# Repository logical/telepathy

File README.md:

THIS PROJECT IS DISCONTINUED FOR NOW.

The research is proving more difficult than I have hoped and there are alternatives available.

This is telepathy the mostly HARDWARE project not telepathy the software project
Sorry for my lack of creativity in choosing a name.

This poject contains an EXPERIMENTAL wireless eeg circuit.

GOAL
------
This project is under development so it is not working. I welcome suggestions.

The goal is to do brain computer interface experments.I want to make a wireless headband that runs
on a battery. 

It contains.

STATUS
------
I made one pcb but it didn't work. I'm still interested in the project so I am currently doing 
a complete redesign of the hardware. I will be etching the boards myself they will be single sided SMT 
and divided in sections.Here are some of the changes I'm planning. 

1. Split the device into sections for power, amplifier and input/output.
2. Replace the wireless module and pic with a wireless capable microcontroller. (telepathy with esp8266?)
3. The whole design will be based on active electrodes.

ELECTRODES: 

I have 2 designs for active electrodes. Active dry electrodes and active noncontact electrodes.
The dry electrodes are based on the openeeg design. The noncontact electrodes are based on a design I found here:

http://www.isn.ucsd.edu/pubs/bsn10.pdf

I'm assuming it is creative commons.

AMPLIFIER BOARD:

The amplifier board is under testing I plan to use one filter for aliasing and filter the rest in software. None
 of the resistor and capacitor values are decided yet.  
I have the source voltage at 3.3v from a cell phone battery. So far I can pick up a heartbeat .

EEGDATA:

A GUI software program for linux that retreives the data from the /dev/rfcomm0 bluetooth serial terminal
and analyzes and displays the data. I started the project in C but it was more convenient to write the data analysis portion in C++. 

On my system I use these commands to setup the bluetooth serial port.

 	#find the address
 	$hcitool scan
	#bind the address
	$sudo rfcomm bind rfcomm0 device_address
	
For BLE

	#find the adapter address
	$hcitool dev
	#find the device address
	$sudo hcitool -i hci0 lescan

Then you need to run any programs that access serial terminal as root unless you have sufficient permission.

FIRMWARE:

The firmware is for a PIC microcontroller 16f1788 and a bluetooth serial module hc-05.

I have wrote a bootloader so I can more easily install firmware.The bootloader sets the hc-05 up at 38400 and waits for a program.
When the program successfully loads it sets a byte in ee memory.when the FLASH command is sent to the program it erases the byte
so the bootloader will again wait for a progam. You can use a standard serial terminal to send the program but you have to set a long delay (~30ms) between characters so the program has time to write. Custom coding the serial interface for the bootloader would be faster but this works for now.

Hopefully I have no glitches in the bootloader or a firmware update could brick the device! 
If so the glitch would have to be fixed and the bootloader reprogrammed.

The microcontroller first sets up the hc-05 at 230400, then wait for a request.When it receives  a request it begins sampling the analog to digital converter and sending the samples to the hc-05.

I have included the makefiles so they should build with the make command but they may require modification . MPLABX should be able to load them as a makefile project but I have not tried.

SCHEMATIC:

I'm developing the amplifier board first. amplifier-board.png is the current design.

DISCLAIMER:

This project is an EXPERIMENT. I make no claims that it actually does anything.It may be harmful to 
individuals or property.
THIS DEVICE AND SOFTWARE MAY BE DANGEROUS. DO NOT BUILD IT.

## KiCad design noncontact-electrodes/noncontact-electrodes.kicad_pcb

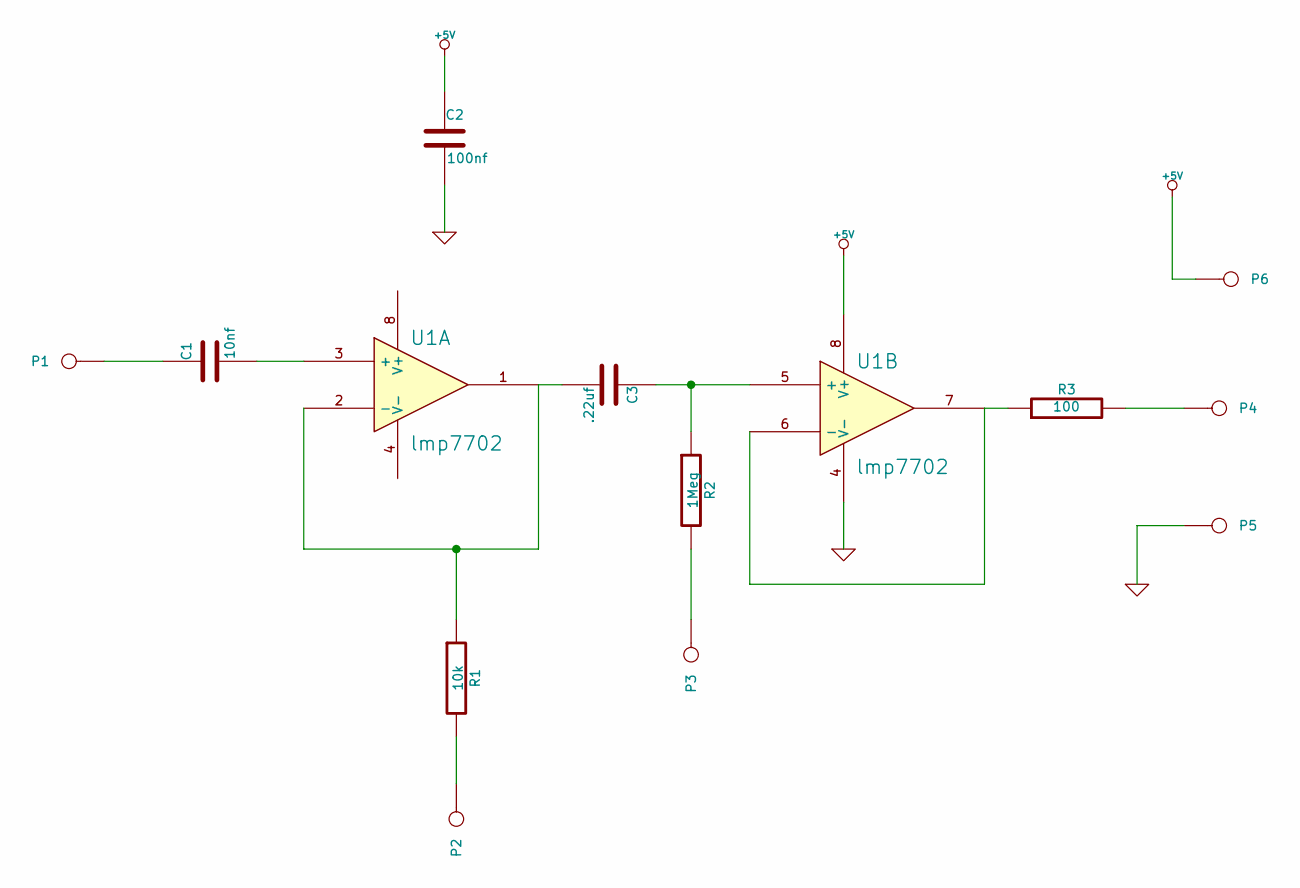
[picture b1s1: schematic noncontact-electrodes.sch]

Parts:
C1: 10nf
C2: 100nf
C3: .22uf
P1, P2, P3, P4, P5, P6: CONN_1
R1: 10k
R2: 1Meg
R3: 100
U1: lmp7702

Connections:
+5V: C2.1, P6.1, U1.8 (V+)
GND: C2.2, P5.1, U1.4 (V-)
unnamed: P2.1, R1.2
unnamed: C1.1, P1.1
unnamed: P4.1, R3.2
unnamed: P3.1, R2.2
unnamed: C1.2, U1.3 (+)
unnamed: C3.2, R1.1, U1.1, U1.2 (-)
unnamed: R3.1, U1.6 (-), U1.7
unnamed: C3.1, R2.1, U1.5 (+)

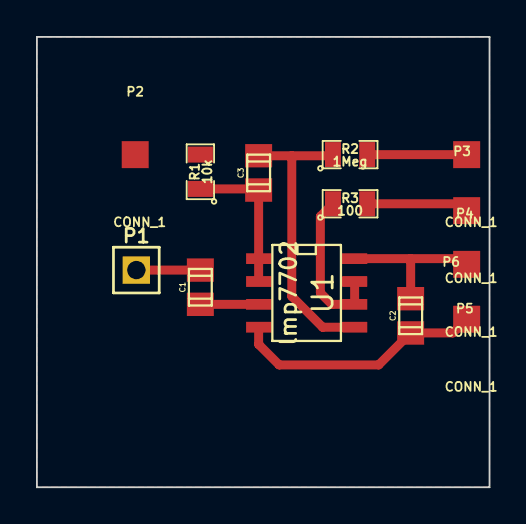
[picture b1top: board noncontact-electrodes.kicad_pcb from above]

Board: 2 copper layers, 25.1 x 25.0 mm, 13 parts (0 on the bottom side), 10 nets.

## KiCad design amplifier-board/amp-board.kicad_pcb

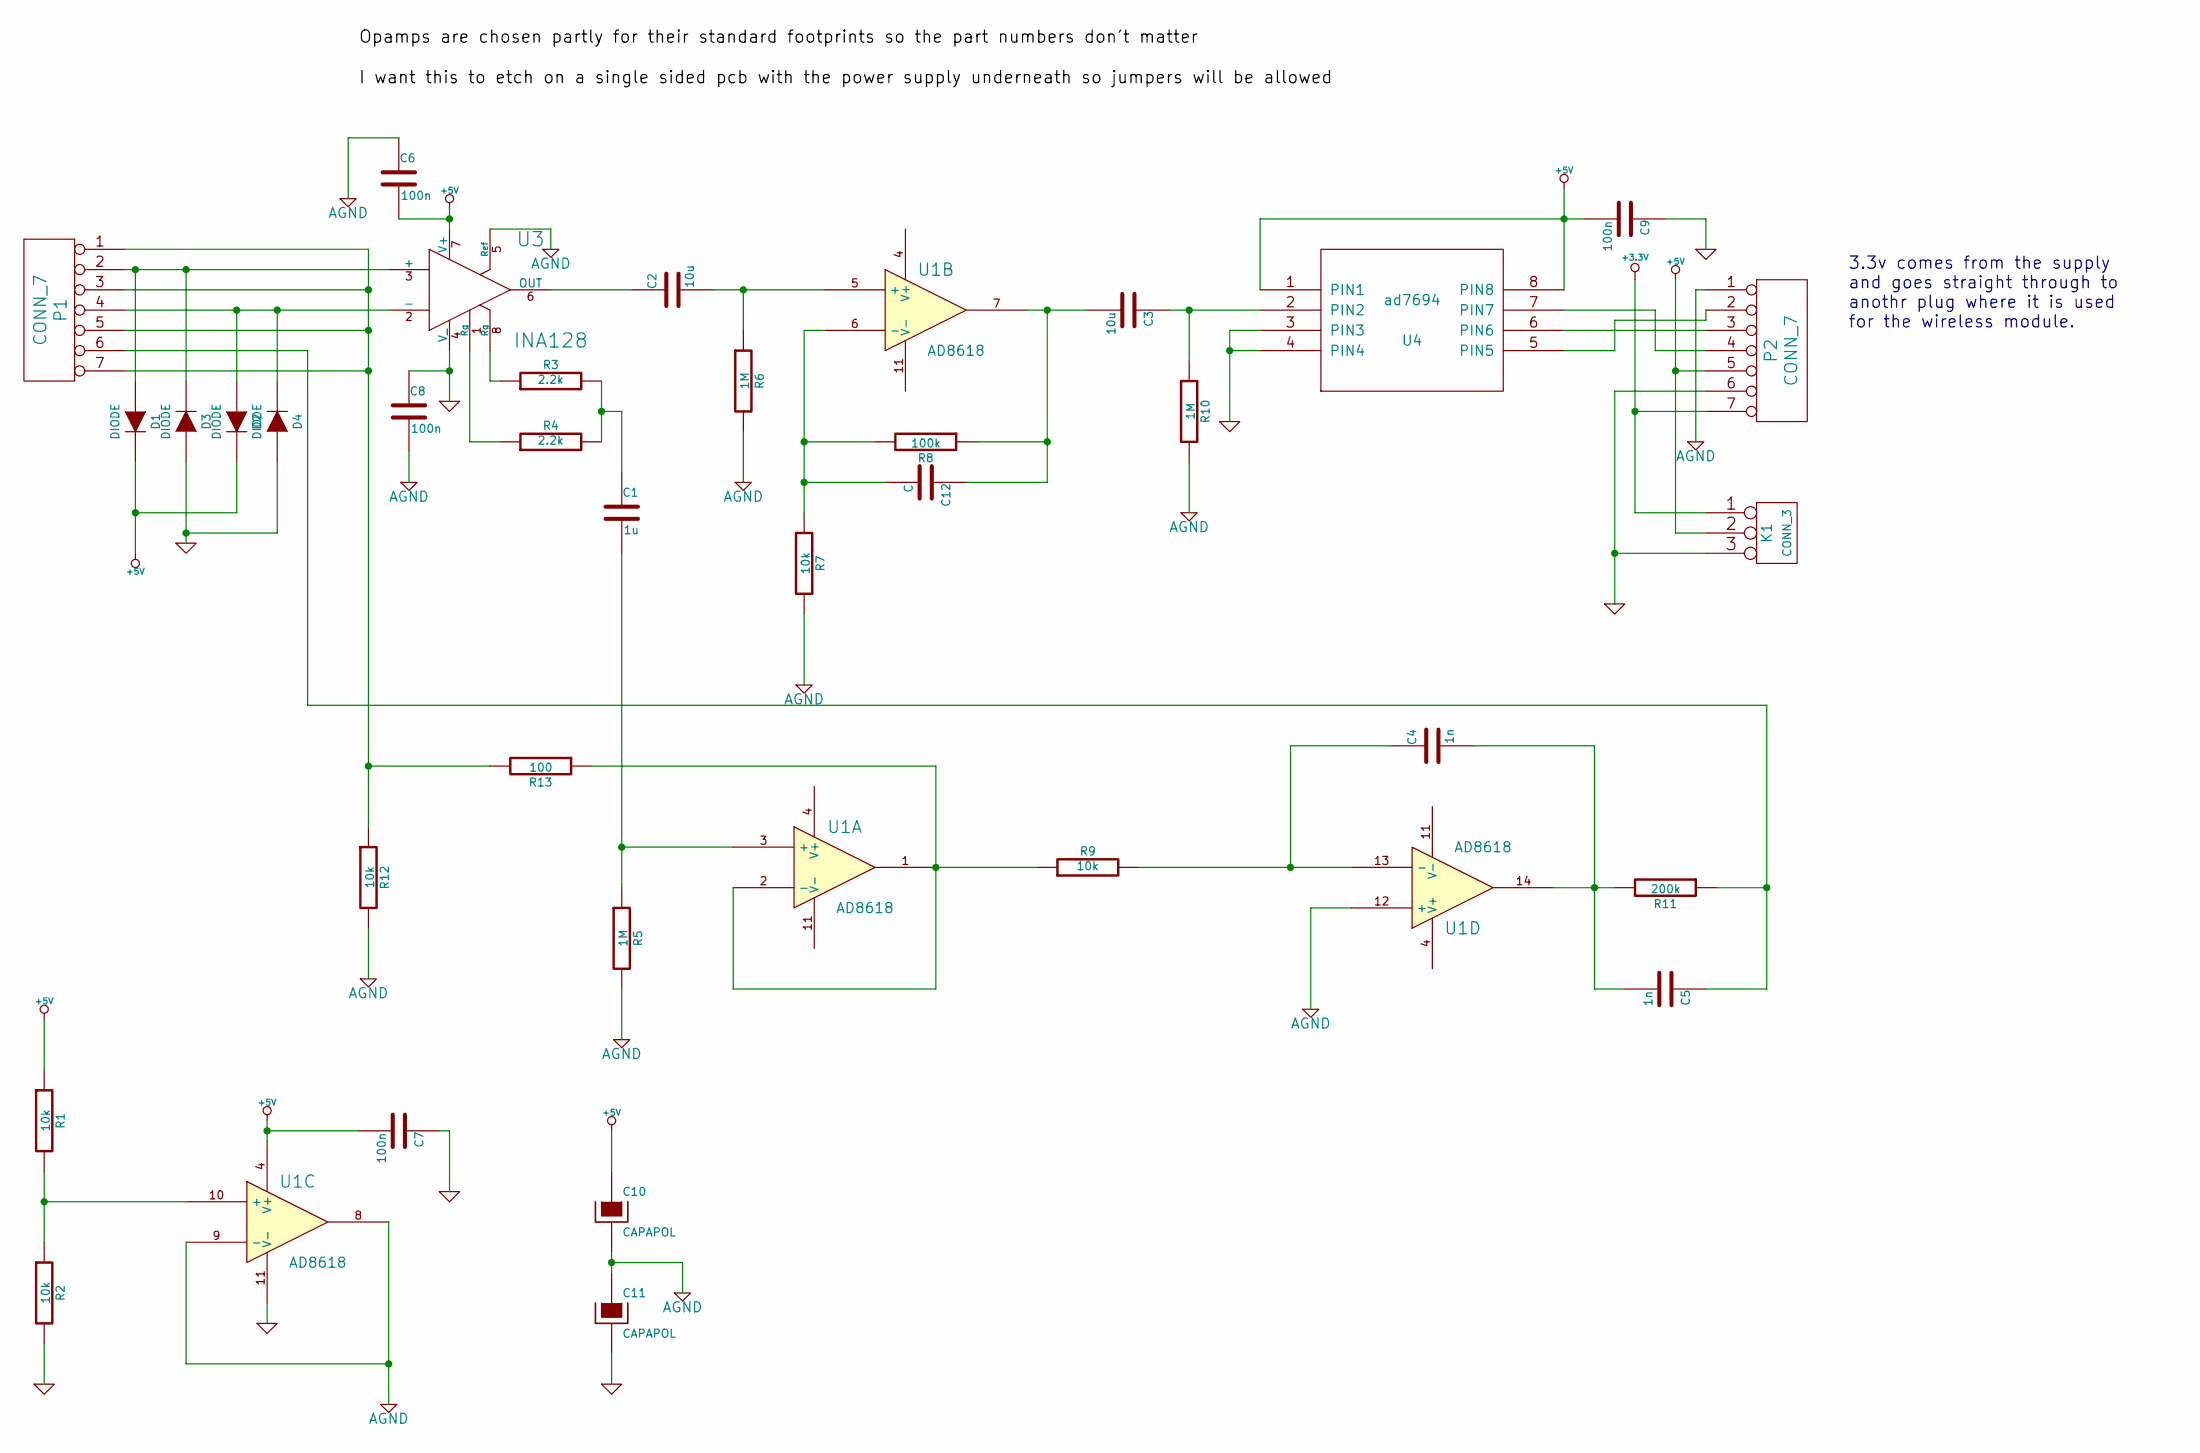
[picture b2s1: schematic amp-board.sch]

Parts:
C1: 1u
C2, C3: 10u
C4, C5: 1n
C6, C7, C8, C9: 100n
C10, C11: CAPAPOL
C12: C
D1, D2, D3, D4: DIODE
K1: CONN_3
P1, P2: CONN_7
R1, R2, R7, R9, R12: 10k
R3, R4: 2.2k
R5, R6, R10: 1M
R8: 100k
R11: 200k
R13: 100
U1: AD8618
U3: INA128
U4: ad7694; MODULE

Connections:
+3.3V: K1.1, P2.7
+5V: C6.2, C7.2, C9.2, C10.1, D1.2 (K), D2.2 (K), K1.2 (PM), P2.5, R1.1, U1.4 (V+), U3.7 (V+), U4.1 (PIN1), U4.8 (PIN8)
AGND: C6.1, C8.2, C10.2, C11.1, P2.1, R5.2, R6.2, R7.2, R10.2, R12.2, U1.8, U1.9 (-), U1.12 (+), U3.5 (Ref)
GND: C7.1, C8.1, C9.1, C11.2, D3.1 (A), D4.1 (A), K1.3, P2.6, R2.2, U1.11 (V-), U3.4 (V_), U4.3 (PIN3), U4.4 (PIN4)
unnamed: R9.1, R13.1, U1.1, U1.2 (-)
unnamed: C4.1, R9.2, U1.13 (-)
unnamed: C4.2, C5.2, R11.2, U1.14
unnamed: C5.1, P1.6, R11.1
unnamed: C1.2, R5.1, U1.3 (+)
unnamed: C1.1, R3.2, R4.2
unnamed: C3.1, R10.1, U4.2 (PIN2)
unnamed: C3.2, C12.1, R8.1, U1.7
unnamed: R1.2, R2.1, U1.10 (+)
unnamed: C2.2, R6.1, U1.5 (+)
unnamed: C2.1, U3.6 (OUT)
unnamed: R4.1, U3.1 (Rg)
unnamed: R3.1, U3.8 (Rg)
unnamed: D2.1 (A), D4.2 (K), P1.4, U3.2 (-)
unnamed: C12.2, R7.1, R8.2, U1.6 (-)
unnamed: D1.1 (A), D3.2 (K), P1.2, U3.3 (+)
unnamed: P2.3, U4.6 (PIN6)
unnamed: P2.2, U4.5 (PIN5)
unnamed: P2.4, U4.7 (PIN7)
unnamed: P1.1, P1.3, P1.5, P1.7, R12.1, R13.2

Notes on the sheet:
3.3v comes from the supply and goes straight through to anothr plug where it is used for the wireless module.

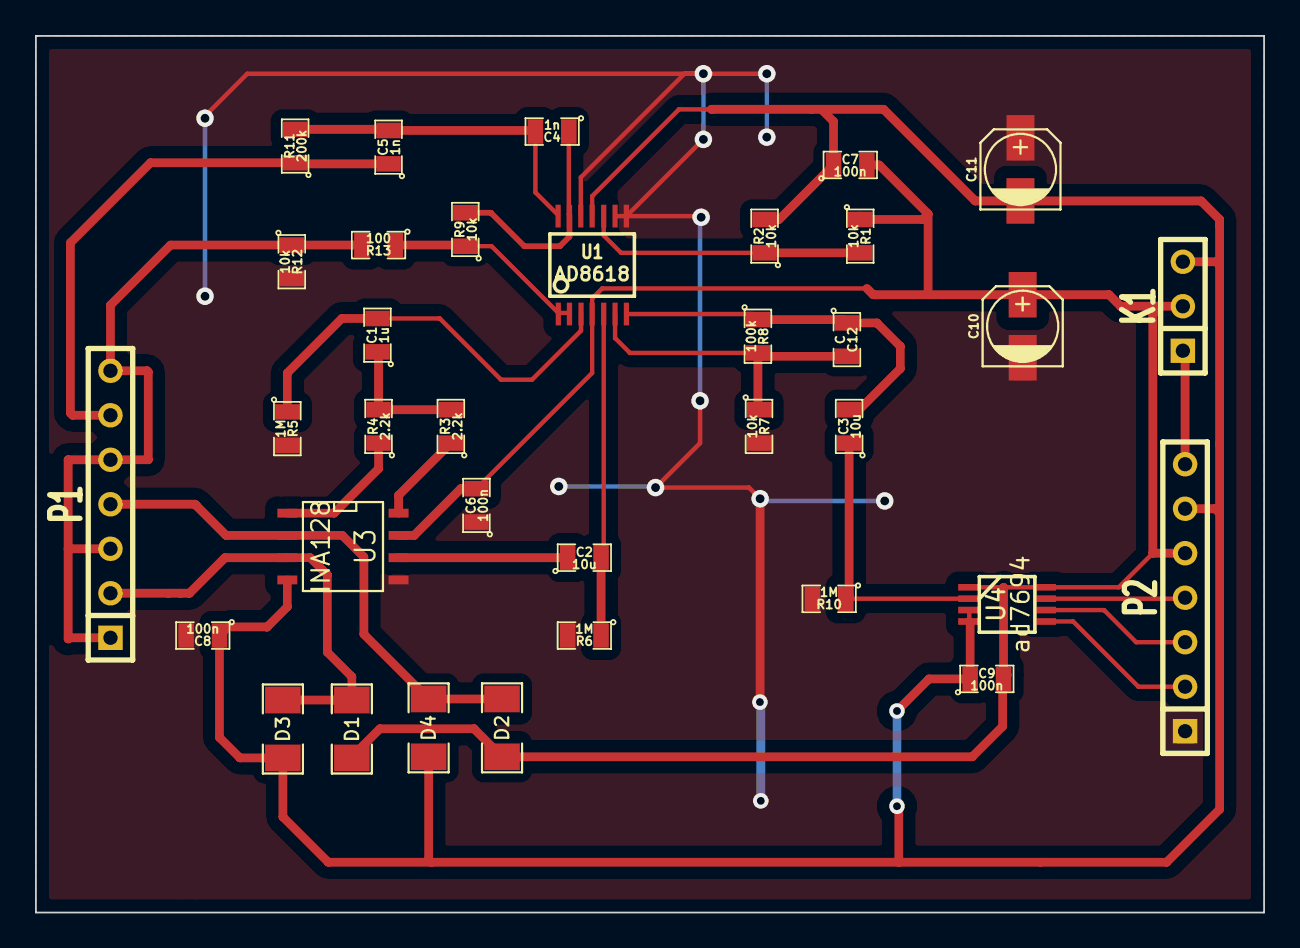
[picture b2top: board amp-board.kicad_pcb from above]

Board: 2 copper layers, 70.1 x 50.0 mm, 35 parts (0 on the bottom side), 24 nets.

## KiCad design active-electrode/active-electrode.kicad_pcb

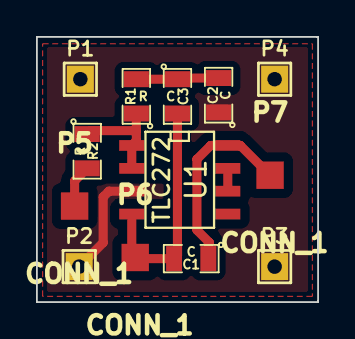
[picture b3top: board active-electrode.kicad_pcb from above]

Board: 2 copper layers, 15.6 x 14.7 mm, 13 parts (0 on the bottom side), 7 nets.

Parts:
C1, C2, C3: C; SM0805
P1, P2, P3, P4: CONN_1; SIL-1
P5, P6, P7: CONN_1; 1PIN_SMD
R1, R2: R; SM0805
U1: TLC272; SO8E

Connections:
+5V: C1.1, P7.1, U1.8
GND: C1.2, C3.2, P6.1, U1.4
unnamed: U1.6, U1.7
unnamed: C2.2, C3.1, R1.2
unnamed: R1.1, R2.1, U1.1, U1.2
unnamed: P5.1, R2.2
unnamed: C2.1, P1.1, P2.1, P3.1, P4.1, U1.3

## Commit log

2014-11-24 fix readme
2014-11-24 added files
2014-12-03 many improvements
2014-12-03 remove .direcory
2015-02-02 remove old file
2015-02-02 made receive parallel a process
2015-02-02 updated firmware
2015-03-14 made program threaded,added circular buffer,added mcp4131 digital pot
2015-03-14 added test waveform, digital pot
2015-03-14 added header
2015-03-18 added schematic
2015-03-20 updated draft schematic
2015-03-23 added kicad files
2015-03-23 added pcb2gcode script
2015-03-24 updated board for cnc mill, added millproject file for pcb2gcode
2015-03-26 increase pad and rack widths , added missing connection
2015-03-27 made board a little smaller
2015-03-28 changed draft schematic
2015-03-29 added a couple capacitors
2015-03-29 update schematic
2015-03-31 changed footprints
2015-03-31 adjusted footprints,added filter components
2015-03-31 added some modules
2015-04-11 first version
2015-04-11 added lib
2015-05-24 added bootloader and makefiles
2015-05-25 still testing bootloader
2015-05-26 cleaned up code
2015-08-23 added noncontact electrodes
2015-08-23 added active electrodes
2016-02-12 added amplifier board
2016-02-15 fixed diodes on amplifier pcb
2016-02-15 changed readme and preview schematic
2018-01-20 added discontinued notice
